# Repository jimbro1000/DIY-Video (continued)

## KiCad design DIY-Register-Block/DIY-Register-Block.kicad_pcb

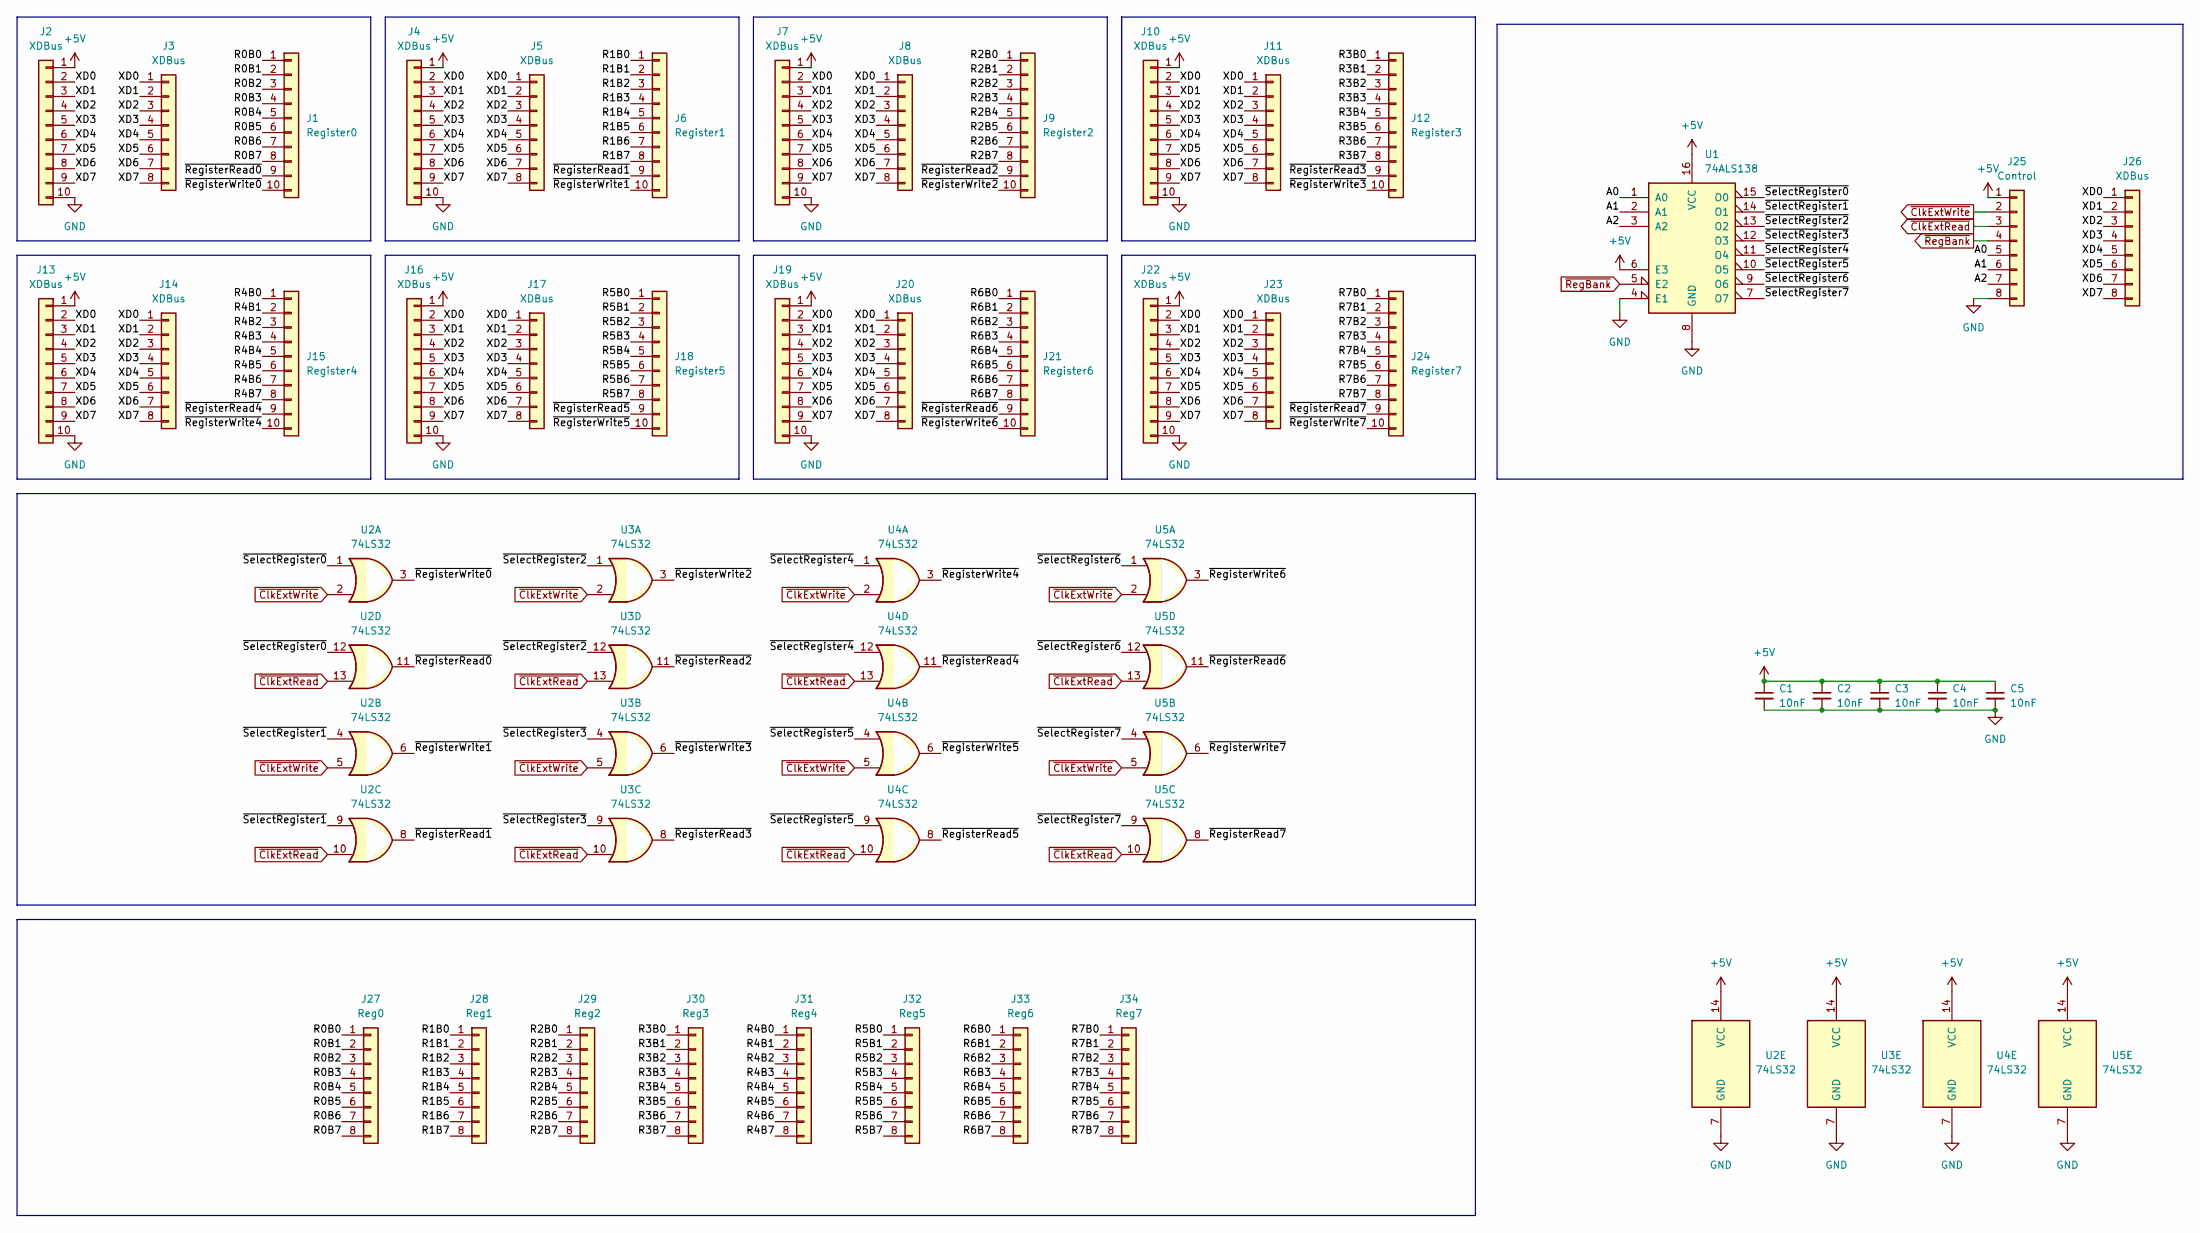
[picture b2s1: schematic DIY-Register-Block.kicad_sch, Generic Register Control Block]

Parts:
C1, C2, C3, C4, C5: 10nF; C_0603_1608Metric
J1: Register0; PinHeader_1x10_P1.27mm_Vertical
J2, J4, J7, J10, J13, J16, J19, J22: XDBus; PinHeader_1x10_P1.27mm_Vertical
J3, J5, J8, J11, J14, J17, J20, J23: XDBus; PinHeader_1x08_P1.27mm_Vertical
J6: Register1; PinHeader_1x10_P1.27mm_Vertical
J9: Register2; PinHeader_1x10_P1.27mm_Vertical
J12: Register3; PinHeader_1x10_P1.27mm_Vertical
J15: Register4; PinHeader_1x10_P1.27mm_Vertical
J18: Register5; PinHeader_1x10_P1.27mm_Vertical
J21: Register6; PinHeader_1x10_P1.27mm_Vertical
J24: Register7; PinHeader_1x10_P1.27mm_Vertical
J25: Control; PinHeader_1x08_P2.54mm_Vertical
J26: XDBus; PinHeader_1x08_P2.54mm_Vertical
J27: Reg0; PinHeader_1x08_P2.54mm_Vertical
J28: Reg1; PinHeader_1x08_P2.54mm_Vertical
J29: Reg2; PinHeader_1x08_P2.54mm_Vertical
J30: Reg3; PinHeader_1x08_P2.54mm_Vertical
J31: Reg4; PinHeader_1x08_P2.54mm_Vertical
J32: Reg5; PinHeader_1x08_P2.54mm_Vertical
J33: Reg6; PinHeader_1x08_P2.54mm_Vertical
J34: Reg7; PinHeader_1x08_P2.54mm_Vertical
U1: 74ALS138; SOIC-16_3.9x9.9mm_P1.27mm
U2, U3, U4: 74LS32; SO-14_3.9x8.65mm_P1.27mm
U5: 74LS32; SOIC-14_3.9x8.7mm_P1.27mm

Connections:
+5V: C1.1, C2.1, C3.1, C4.1, C5.1, J2.1, J4.1, J7.1, J10.1, J13.1, J16.1, J19.1, J22.1, J25.1, U1.6 (E3), U1.16 (VCC), U2.14 (VCC), U3.14 (VCC), U4.14 (VCC), U5.14 (VCC)
/A0: J25.5, U1.1 (A0)
/A1: J25.6, U1.2 (A1)
/A2: J25.7, U1.3 (A2)
/R0B0: J1.1, J27.1
/R0B1: J1.2, J27.2
/R0B2: J1.3, J27.3
/R0B3: J1.4, J27.4
/R0B4: J1.5, J27.5
/R0B5: J1.6, J27.6
/R0B6: J1.7, J27.7
/R0B7: J1.8, J27.8
/R1B0: J6.1, J28.1
/R1B1: J6.2, J28.2
/R1B2: J6.3, J28.3
/R1B3: J6.4, J28.4
/R1B4: J6.5, J28.5
/R1B5: J6.6, J28.6
/R1B6: J6.7, J28.7
/R1B7: J6.8, J28.8
/R2B0: J9.1, J29.1
/R2B1: J9.2, J29.2
/R2B2: J9.3, J29.3
/R2B3: J9.4, J29.4
/R2B4: J9.5, J29.5
/R2B5: J9.6, J29.6
/R2B6: J9.7, J29.7
/R2B7: J9.8, J29.8
/R3B0: J12.1, J30.1
/R3B1: J12.2, J30.2
/R3B2: J12.3, J30.3
/R3B3: J12.4, J30.4
/R3B4: J12.5, J30.5
/R3B5: J12.6, J30.6
/R3B6: J12.7, J30.7
/R3B7: J12.8, J30.8
/R4B0: J15.1, J31.1
/R4B1: J15.2, J31.2
/R4B2: J15.3, J31.3
/R4B3: J15.4, J31.4
/R4B4: J15.5, J31.5
/R4B5: J15.6, J31.6
/R4B6: J15.7, J31.7
/R4B7: J15.8, J31.8
/R5B0: J18.1, J32.1
/R5B1: J18.2, J32.2
/R5B2: J18.3, J32.3
/R5B3: J18.4, J32.4
/R5B4: J18.5, J32.5
/R5B5: J18.6, J32.6
/R5B6: J18.7, J32.7
/R5B7: J18.8, J32.8
/R6B0: J21.1, J33.1
/R6B1: J21.2, J33.2
/R6B2: J21.3, J33.3
/R6B3: J21.4, J33.4
/R6B4: J21.5, J33.5
/R6B5: J21.6, J33.6
/R6B6: J21.7, J33.7
/R6B7: J21.8, J33.8
/R7B0: J24.1, J34.1
/R7B1: J24.2, J34.2
/R7B2: J24.3, J34.3
/R7B3: J24.4, J34.4
/R7B4: J24.5, J34.5
/R7B5: J24.6, J34.6
/R7B6: J24.7, J34.7
/R7B7: J24.8, J34.8
/XD0: J2.2, J3.1, J4.2, J5.1, J7.2, J8.1, J10.2, J11.1, J13.2, J14.1, J16.2, J17.1, J19.2, J20.1, J22.2, J23.1, J26.1
/XD1: J2.3, J3.2, J4.3, J5.2, J7.3, J8.2, J10.3, J11.2, J13.3, J14.2, J16.3, J17.2, J19.3, J20.2, J22.3, J23.2, J26.2
/XD2: J2.4, J3.3, J4.4, J5.3, J7.4, J8.3, J10.4, J11.3, J13.4, J14.3, J16.4, J17.3, J19.4, J20.3, J22.4, J23.3, J26.3
/XD3: J2.5, J3.4, J4.5, J5.4, J7.5, J8.4, J10.5, J11.4, J13.5, J14.4, J16.5, J17.4, J19.5, J20.4, J22.5, J23.4, J26.4
/XD4: J2.6, J3.5, J4.6, J5.5, J7.6, J8.5, J10.6, J11.5, J13.6, J14.5, J16.6, J17.5, J19.6, J20.5, J22.6, J23.5, J26.5
/XD5: J2.7, J3.6, J4.7, J5.6, J7.7, J8.6, J10.7, J11.6, J13.7, J14.6, J16.7, J17.6, J19.7, J20.6, J22.7, J23.6, J26.6
/XD6: J2.8, J3.7, J4.8, J5.7, J7.8, J8.7, J10.8, J11.7, J13.8, J14.7, J16.8, J17.7, J19.8, J20.7, J22.8, J23.7, J26.7
/XD7: J2.9, J3.8, J4.9, J5.8, J7.9, J8.8, J10.9, J11.8, J13.9, J14.8, J16.9, J17.8, J19.9, J20.8, J22.9, J23.8, J26.8
/~RegisterRead0: J1.9, U2.11
/~RegisterRead1: J6.9, U2.8
/~RegisterRead2: J9.9, U3.11
/~RegisterRead3: J12.9, U3.8
/~RegisterRead4: J15.9, U4.11
/~RegisterRead5: J18.9, U4.8
/~RegisterRead6: J21.9, U5.11
/~RegisterRead7: J24.9, U5.8
/~RegisterWrite0: J1.10, U2.3
/~RegisterWrite1: J6.10, U2.6
/~RegisterWrite2: J9.10, U3.3
/~RegisterWrite3: J12.10, U3.6
/~RegisterWrite4: J15.10, U4.3
/~RegisterWrite5: J18.10, U4.6
/~RegisterWrite6: J21.10, U5.3
/~RegisterWrite7: J24.10, U5.6
/~SelectRegister0: U1.15 (O0), U2.1, U2.12
/~SelectRegister1: U1.14 (O1), U2.4, U2.9
/~SelectRegister2: U1.13 (O2), U3.1, U3.12
/~SelectRegister3: U1.12 (O3), U3.4, U3.9
/~SelectRegister4: U1.11 (O4), U4.1, U4.12
/~SelectRegister5: U1.10 (O5), U4.4, U4.9
/~SelectRegister6: U1.9 (O6), U5.1, U5.12
/~SelectRegister7: U1.7 (O7), U5.4, U5.9
GND: C1.2, C2.2, C3.2, C4.2, C5.2, J2.10, J4.10, J7.10, J10.10, J13.10, J16.10, J19.10, J22.10, J25.8, U1.4 (E1), U1.8 (GND), U2.7 (GND), U3.7 (GND), U4.7 (GND), U5.7 (GND)
~ClkExtRead: J25.3, U2.10, U2.13, U3.10, U3.13, U4.10, U4.13, U5.10, U5.13
~ClkExtWrite: J25.2, U2.2, U2.5, U3.2, U3.5, U4.2, U4.5, U5.2, U5.5
~RegBank: J25.4, U1.5 (E2)

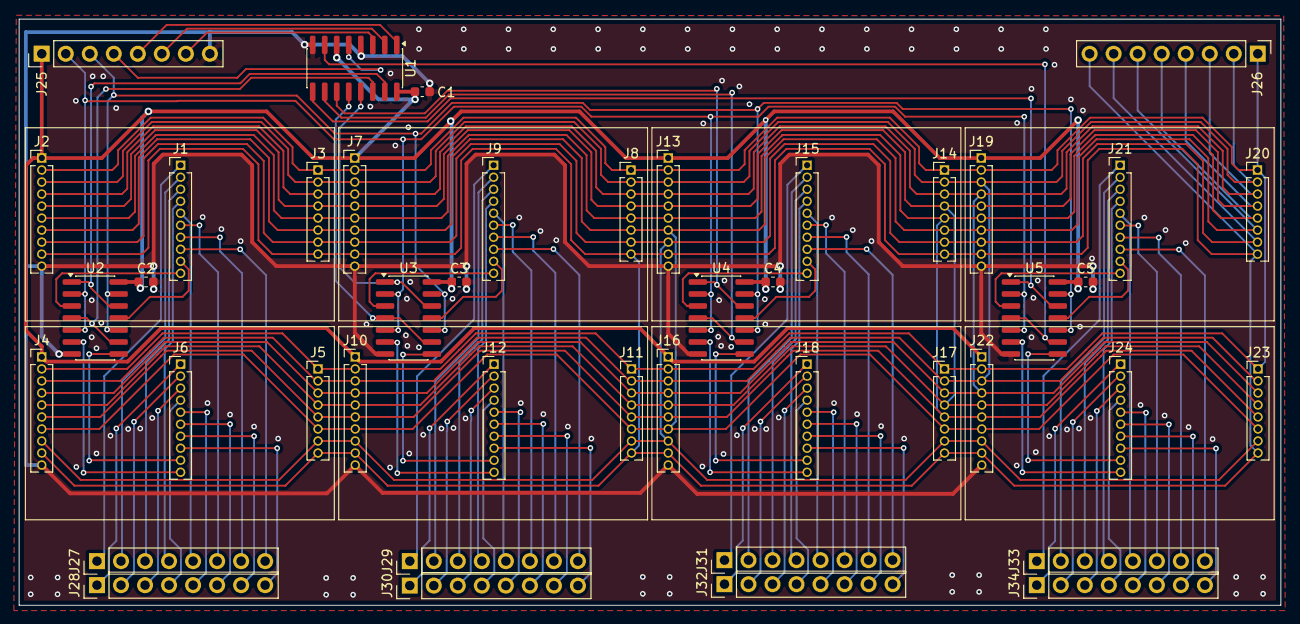
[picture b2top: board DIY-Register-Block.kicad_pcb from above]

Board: 2 copper layers, 133.4 x 62.0 mm, 44 parts (0 on the bottom side), 104 nets.

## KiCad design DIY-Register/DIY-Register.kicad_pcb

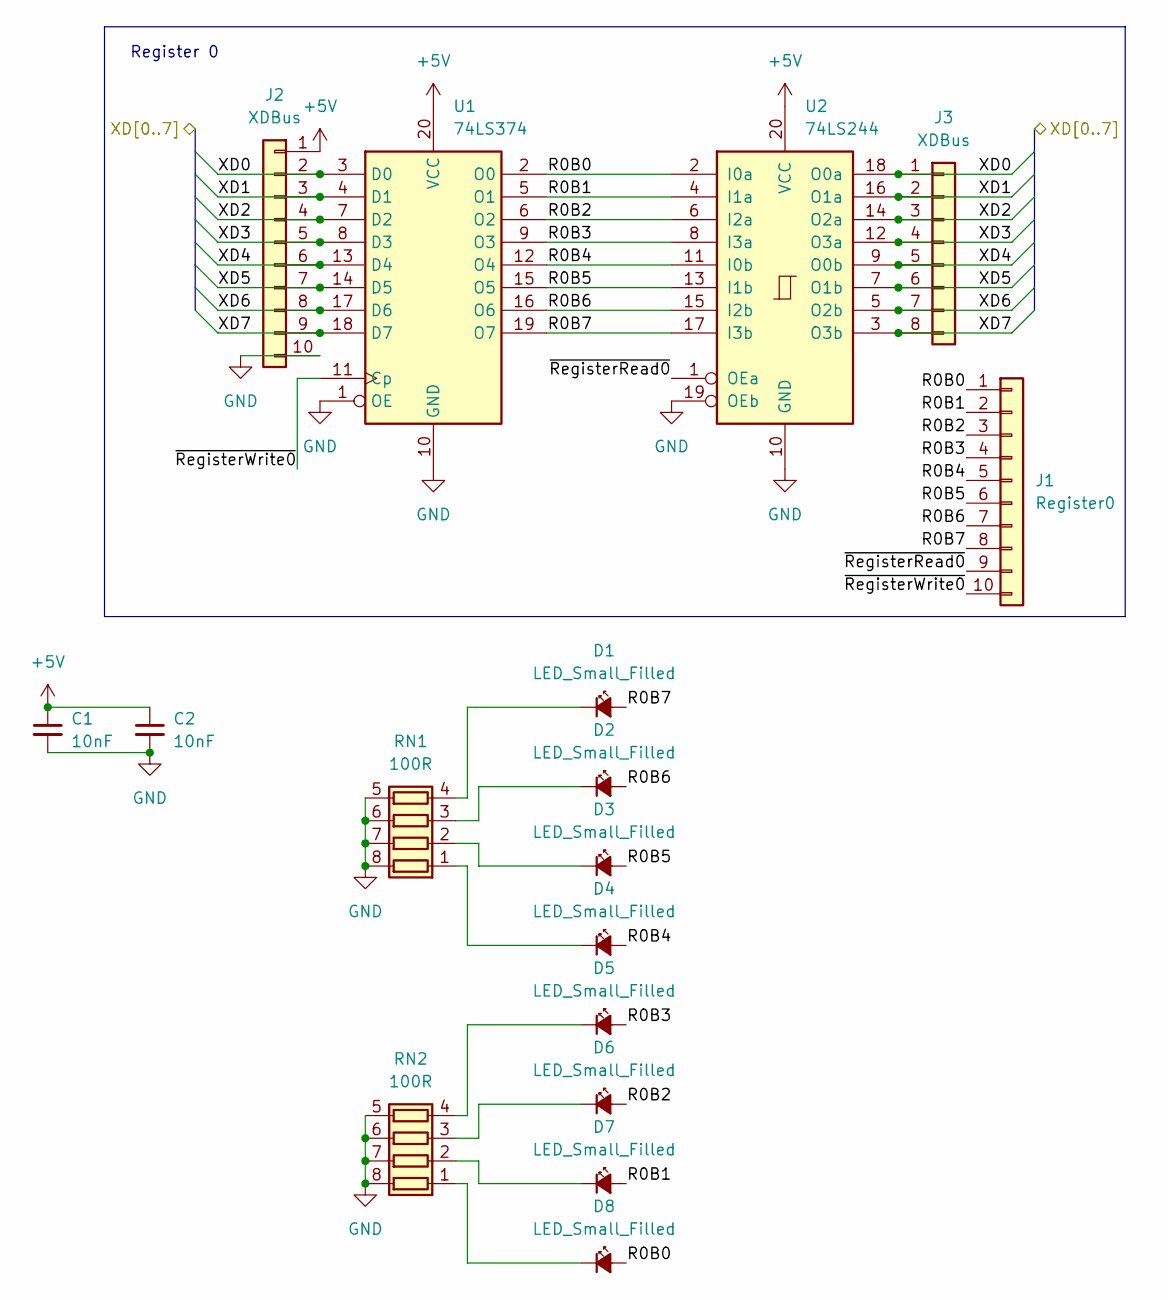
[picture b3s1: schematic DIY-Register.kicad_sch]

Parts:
C1, C2: 10nF; C_0603_1608Metric
D1, D2, D3, D4, D5, D6, D7, D8: LED_Small_Filled; LED_0603_1608Metric
J1: Register0; PinHeader_1x10_P1.27mm_Vertical
J2: XDBus; PinHeader_1x10_P1.27mm_Vertical
J3: XDBus; PinHeader_1x08_P1.27mm_Vertical
RN1, RN2: 100R; R_Array_Concave_4x0402
U1: 74LS374; SO-20_5.3x12.6mm_P1.27mm
U2: 74LS244; SO-20_5.3x12.6mm_P1.27mm

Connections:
+5V: C1.1, C2.1, J2.1, U1.20 (VCC), U2.20 (VCC)
/R0B0: D8.2 (A), J1.1, U1.2 (O0), U2.2 (I0a)
/R0B1: D7.2 (A), J1.2, U1.5 (O1), U2.4 (I1a)
/R0B2: D6.2 (A), J1.3, U1.6 (O2), U2.6 (I2a)
/R0B3: D5.2 (A), J1.4, U1.9 (O3), U2.8 (I3a)
/R0B4: D4.2 (A), J1.5, U1.12 (O4), U2.11 (I0b)
/R0B5: D3.2 (A), J1.6, U1.15 (O5), U2.13 (I1b)
/R0B6: D2.2 (A), J1.7, U1.16 (O6), U2.15 (I2b)
/R0B7: D1.2 (A), J1.8, U1.19 (O7), U2.17 (I3b)
/XD0: J2.2, J3.1, U1.3 (D0), U2.18 (O0a)
/XD1: J2.3, J3.2, U1.4 (D1), U2.16 (O1a)
/XD2: J2.4, J3.3, U1.7 (D2), U2.14 (O2a)
/XD3: J2.5, J3.4, U1.8 (D3), U2.12 (O3a)
/XD4: J2.6, J3.5, U1.13 (D4), U2.9 (O0b)
/XD5: J2.7, J3.6, U1.14 (D5), U2.7 (O1b)
/XD6: J2.8, J3.7, U1.17 (D6), U2.5 (O2b)
/XD7: J2.9, J3.8, U1.18 (D7), U2.3 (O3b)
/~RegisterRead0: J1.9, U2.1 (OEa)
/~RegisterWrite0: J1.10, U1.11 (Cp)
GND: C1.2, C2.2, J2.10, RN1.5 (R4.2), RN1.6 (R3.2), RN1.7 (R2.2), RN1.8 (R1.2), RN2.5 (R4.2), RN2.6 (R3.2), RN2.7 (R2.2), RN2.8 (R1.2), U1.1 (OE), U1.10 (GND), U2.10 (GND), U2.19 (OEb)
unnamed: D1.1 (K), RN1.4 (R4.1)
unnamed: D2.1 (K), RN1.3 (R3.1)
unnamed: D3.1 (K), RN1.2 (R2.1)
unnamed: D4.1 (K), RN1.1 (R1.1)
unnamed: D5.1 (K), RN2.4 (R4.1)
unnamed: D6.1 (K), RN2.3 (R3.1)
unnamed: D7.1 (K), RN2.2 (R2.1)
unnamed: D8.1 (K), RN2.1 (R1.1)

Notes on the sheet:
Register 0

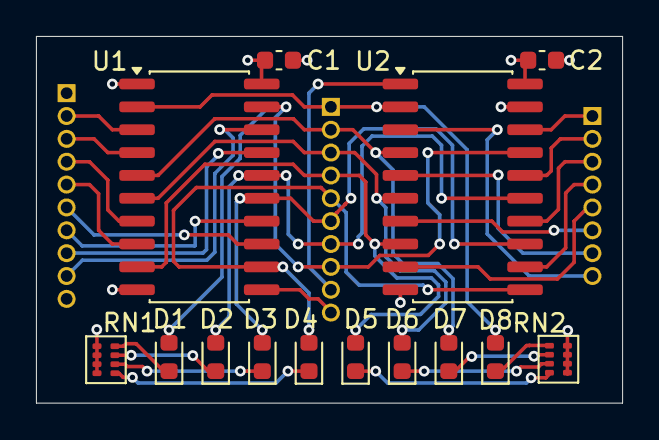
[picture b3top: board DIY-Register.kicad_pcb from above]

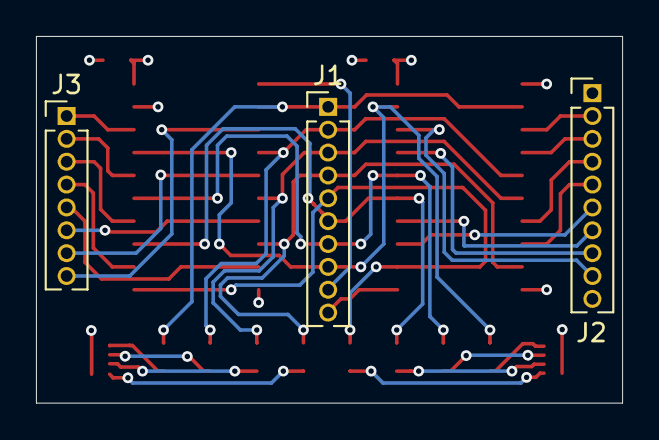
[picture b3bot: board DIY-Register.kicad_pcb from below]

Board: 4 copper layers, 32.6 x 20.4 mm, 17 parts (3 on the bottom side), 28 nets.

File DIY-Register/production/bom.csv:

Designator,Footprint,Quantity,Value,LCSC Part #
"C1, C2",0603,2,10nF,
"D1, D2, D3, D4, D5, D6, D7, D8",0603,8,LED_Small_Filled,
J1,PinHeader_1x10_P1.27mm_Vertical,1,Register0,
J2,PinHeader_1x10_P1.27mm_Vertical,1,XDBus,
J3,PinHeader_1x08_P1.27mm_Vertical,1,XDBus,
"RN1, RN2",R_Array_Concave_4x0402,2,100R,
U1,SO-20_5.3x12.6mm_P1.27mm,1,74LS374,
U2,SO-20_5.3x12.6mm_P1.27mm,1,74LS244,
